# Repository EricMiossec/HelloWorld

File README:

This is the repo for our NXT laser range finder. So far we have been unable to make it work with our current setup. Right now we are working on improving the PCB layout. We might also use this repo to make other NXT sensor, hence the generic "NXT-Sensor" repo name.

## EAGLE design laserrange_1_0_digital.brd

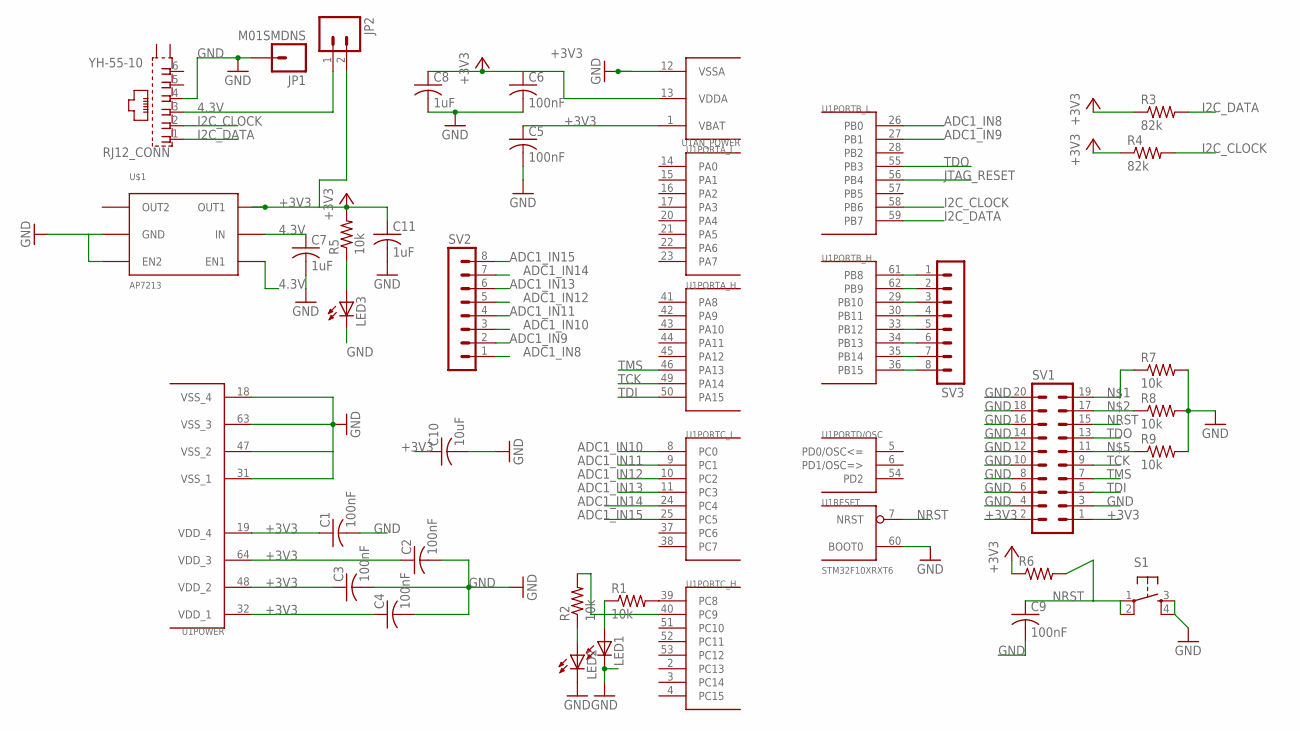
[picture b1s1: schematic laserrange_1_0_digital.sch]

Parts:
C1, C2, C3, C4, C5, C6, C9: 100nF; C0603
C7, C8, C11: 1uF; C0603
C10: 10uF; C0805
JP1: M01SMDNS; 1X01NS
JP2: M02PTH; 1X02
LED1, LED2, LED3: LEDCHIPLED_0805; CHIPLED_0805
R1, R2, R5, R7, R8, R9: 10k; R0805
R3, R4: 82k; R0805
R6: R-US_R0805; R0805
RJ12_CONN: YH-55-10
S1: TAC_SWITCHPTH; TACTILE-PTH
SV1: MA10-2
SV2, SV3: MA08-1
U1: STM32F10XRXT6; TQFP64
U$1: AP7213; SOT23-6

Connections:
4.3V: C7.1, JP2.1, RJ12_CONN.3, U$1.4 (EN1), U$1.5 (IN)
+3V3: C1.1, C2.1, C3.1, C4.1, C5.1, C6.1, C8.1, C10.1, C11.1, JP2.2, R3.1, R4.1, R5.2, R6.1, SV1.1, SV1.2, U1.1 (VBAT), U1.13 (VDDA), U1.19 (VDD_4), U1.32 (VDD_1), U1.48 (VDD_2), U1.64 (VDD_3), U$1.6 (OUT1)
ADC1_IN8: SV2.1, U1.26 (PB0)
ADC1_IN9: SV2.2, U1.27 (PB1)
ADC1_IN10: SV2.3, U1.8 (PC0)
ADC1_IN11: SV2.4, U1.9 (PC1)
ADC1_IN12: SV2.5, U1.10 (PC2)
ADC1_IN13: SV2.6, U1.11 (PC3)
ADC1_IN14: SV2.7, U1.24 (PC4)
ADC1_IN15: SV2.8, U1.25 (PC5)
GND: C1.2, C2.2, C3.2, C4.2, C5.2, C6.2, C7.2, C8.2, C9.2, C10.2, C11.2, JP1.1, LED1.C, LED2.C, LED3.C, R7.2, R8.2, R9.2, RJ12_CONN.4, S1.3, S1.4, SV1.3, SV1.4, SV1.6, SV1.8, SV1.10, SV1.12, SV1.14, SV1.16, SV1.18, SV1.20, U1.12 (VSSA), U1.18 (VSS_4), U1.31 (VSS_1), U1.47 (VSS_2), U1.60 (BOOT0), U1.63 (VSS_3), U$1.2 (GND), U$1.3 (EN2)
I2C_CLOCK: R4.2, RJ12_CONN.2, U1.58 (PB6)
I2C_DATA: R3.2, RJ12_CONN.1, U1.59 (PB7)
JTAG_RESET: U1.56 (PB4)
unnamed: R7.1, SV1.19
unnamed: R8.1, SV1.17
unnamed: SV3.1, U1.61 (PB8)
unnamed: SV3.2, U1.62 (PB9)
unnamed: R9.1, SV1.11
unnamed: SV3.3, U1.29 (PB10)
unnamed: SV3.4, U1.30 (PB11)
unnamed: SV3.5, U1.33 (PB12)
unnamed: SV3.6, U1.34 (PB13)
unnamed: SV3.7, U1.35 (PB14)
unnamed: SV3.8, U1.36 (PB15)
unnamed: R1.2, U1.39 (PC8)
unnamed: LED1.A, R1.1
unnamed: LED3.A, R5.1
unnamed: LED2.A, R2.1
unnamed: R2.2, U1.40 (PC9)
NRST: C9.1, R6.2, S1.1, S1.2, SV1.15, U1.7 (NRST)
TCK: SV1.9, U1.49 (PA14)
TDI: SV1.5, U1.50 (PA15)
TDO: SV1.13, U1.55 (PB3)
TMS: SV1.7, U1.46 (PA13)

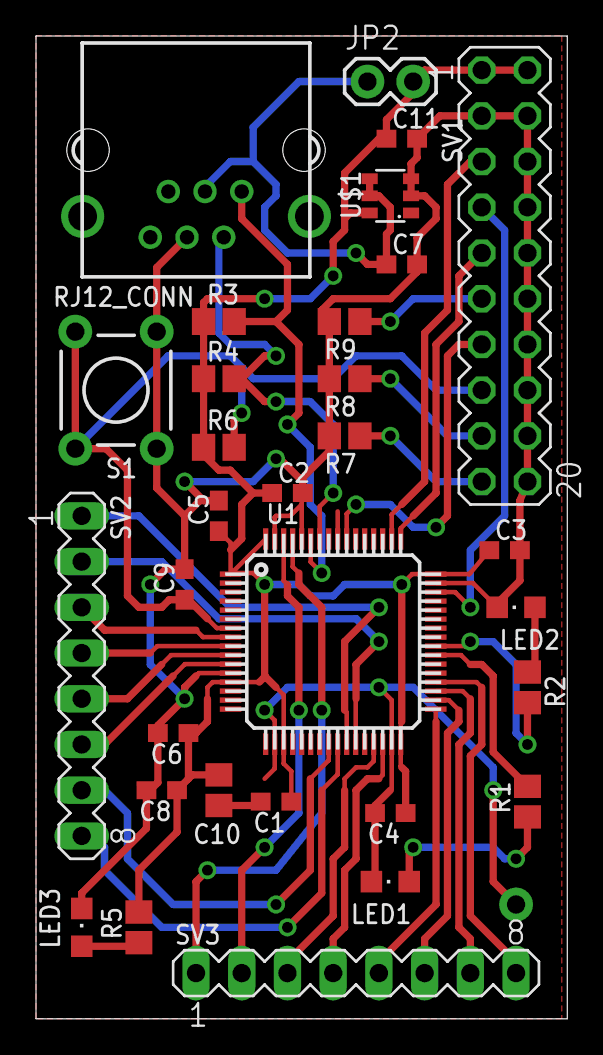
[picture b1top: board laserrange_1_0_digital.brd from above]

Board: 2 copper layers, 29.5 x 54.6 mm, 32 parts (0 on the bottom side), 34 nets.

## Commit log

2012-06-15 Initial commit into github
2012-06-15 Initial commit of the files from the old directory
2012-06-15 Fixed the RJ12 connector footpad connections
2012-07-16 Ignore file

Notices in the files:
parts and their libraries:
SparkFun: Licensing: CC v3.0 Share-Alike You are welcome to use this library for commercial purposes.
